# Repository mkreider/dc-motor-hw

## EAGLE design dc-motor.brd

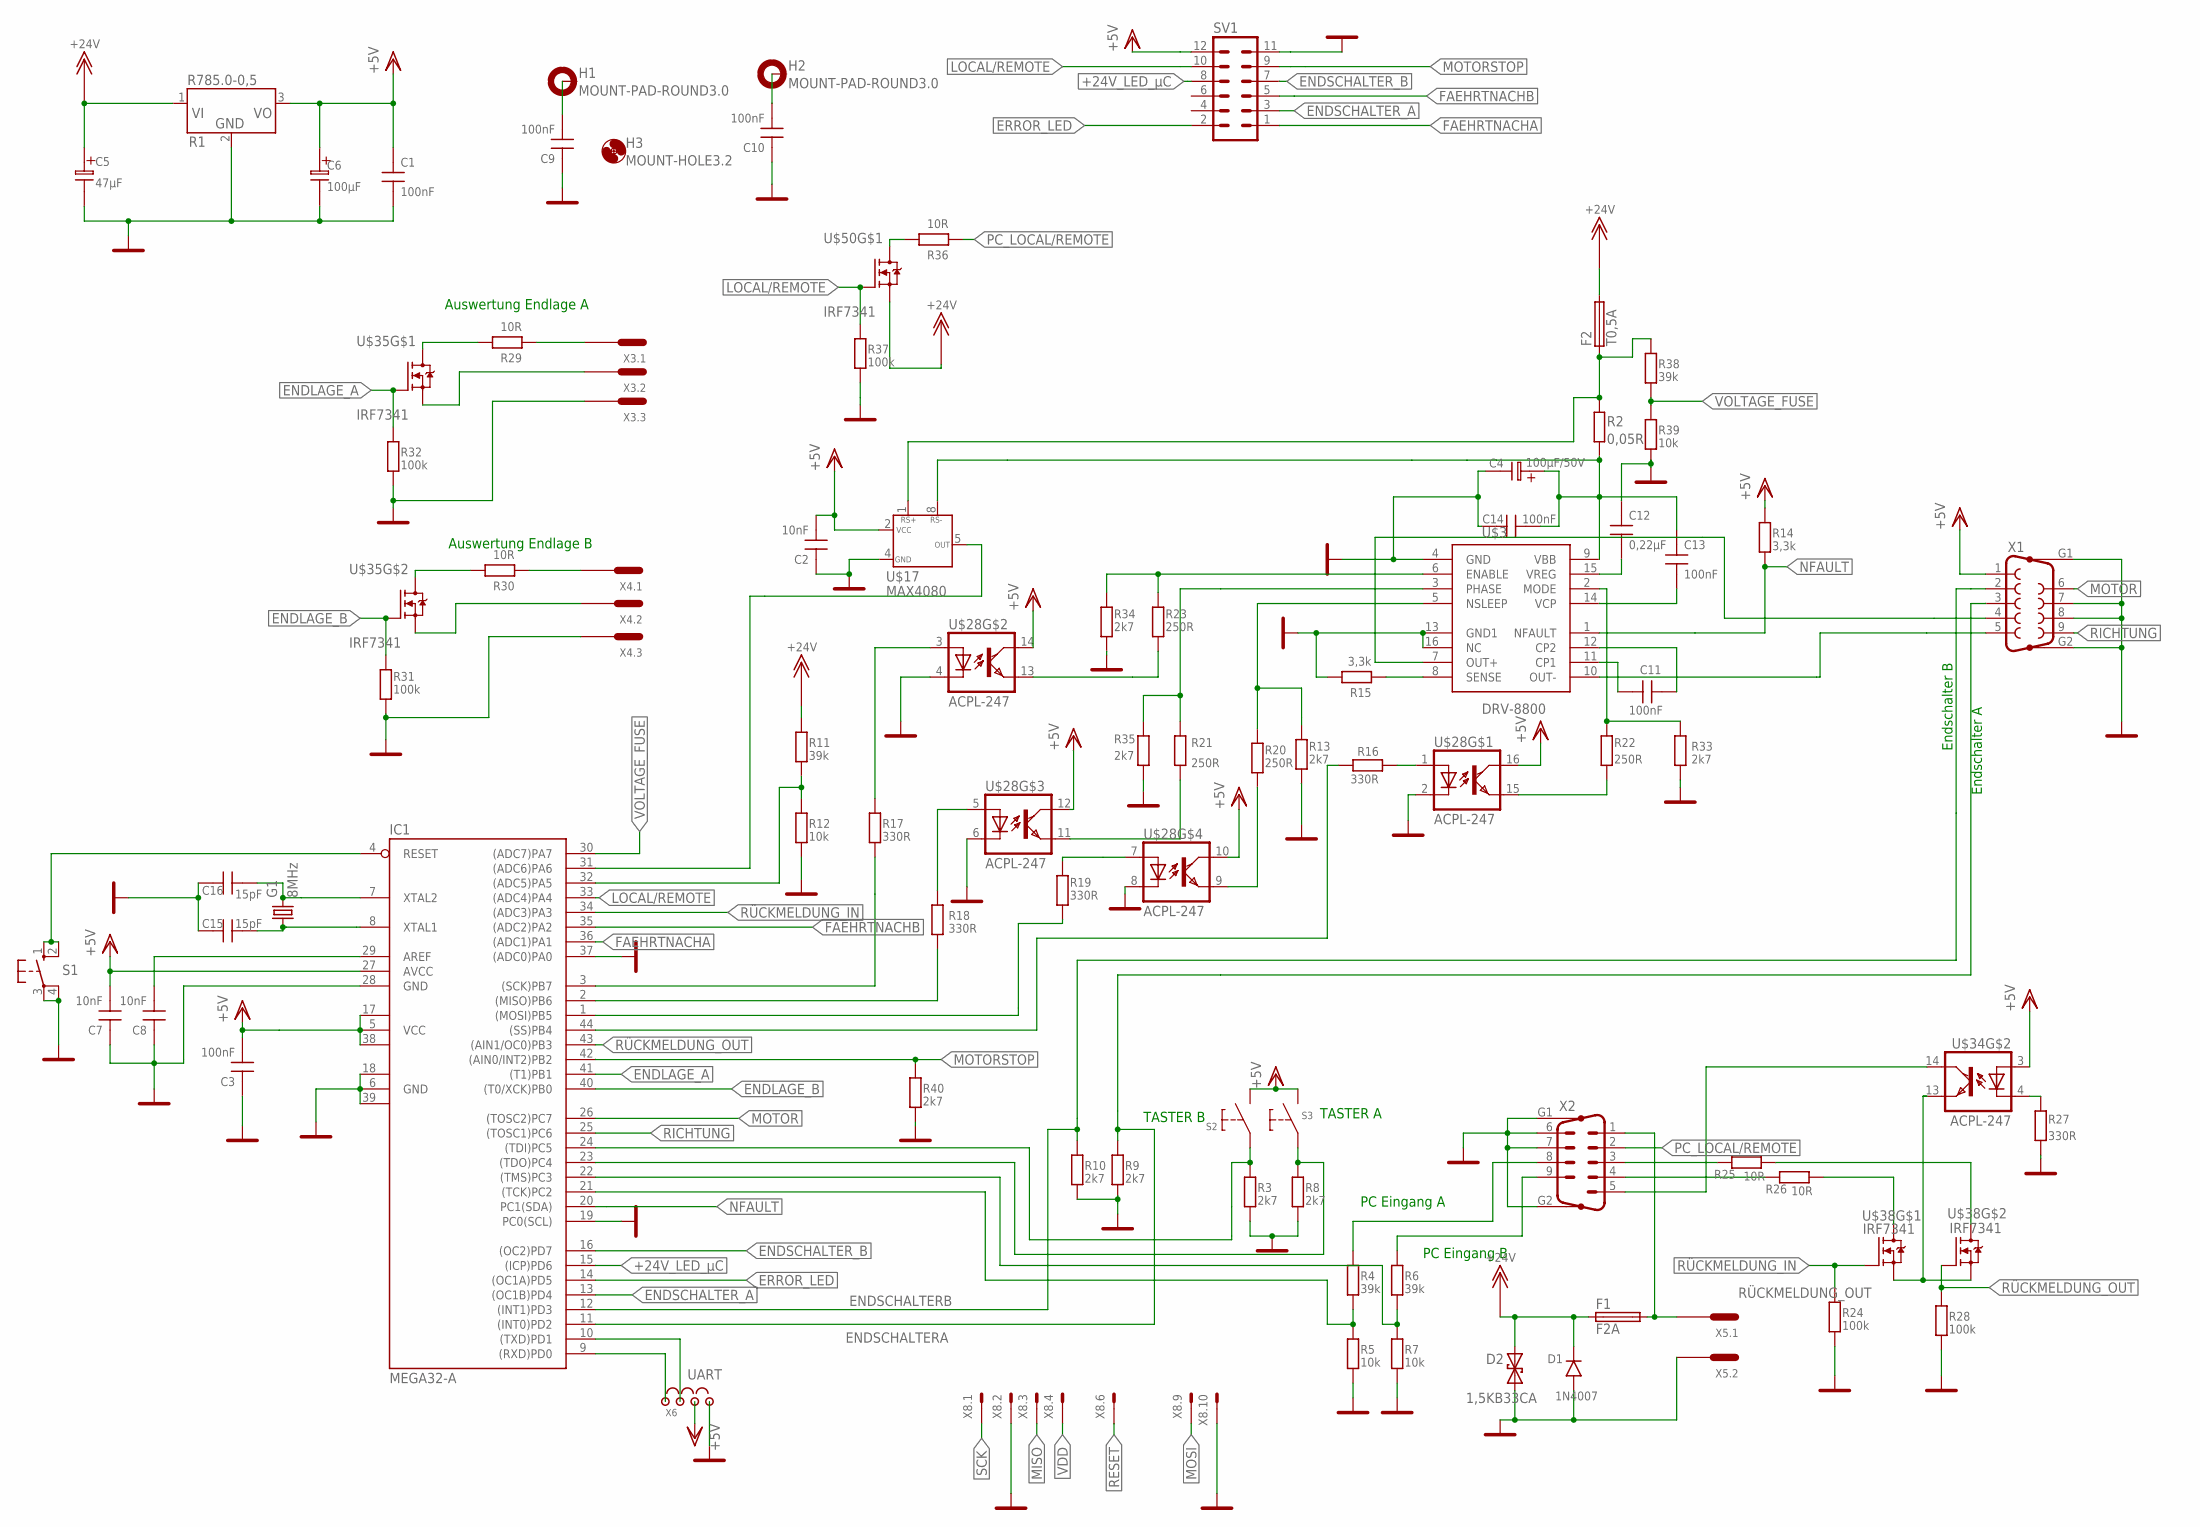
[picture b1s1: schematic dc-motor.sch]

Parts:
C1, C3, C9, C10, C11, C13, C14: 100nF; 0805
C2, C7, C8: 10nF; 0805
C4: 100µF/50V; E5-13
C5: 47µF; E5-13
C6: 100µF; E5-13
C12: 0,22µF; 0805
C15, C16: 15pF; 0805
D1: 1N4007; RM10DR1
D2: 1,5KB33CA; CB417-15
F1: F2A; F457
F2: T0,5A; F457
G1: 8MHz; HC18U-V
H1, H2: MOUNT-PAD-ROUND3.0; 3,0-PAD
H3: MOUNT-HOLE3.2; 3,2
IC1: MEGA32-A; TQFP44; MPN ATMEGA32-16AU
R1: R785.0-0,5; SIP3
R2: 0,05R; SMS-0
R3, R8, R9, R10, R13, R33, R34, R35, R40: 2k7; 0805
R4, R6, R11, R38: 39k; 0805
R5, R7, R12, R39: 10k; 0805
R14, R15: 3,3k; 0805
R16, R17, R18, R19, R27: 330R; 0805
R20, R21, R22, R23: 250R; 0805
R24, R28, R31, R32, R37: 100k; 0805
R25, R26, R29, R30, R36: 10R; 0805
S1: 10-XX; B3F-10XX
S2, S3: DRUCKTASTER_ABGW; 1_POL_ABGW
SV1: MA06-2
U$3: DRV-8800; TSSOP16
U$17: MAX4080
U$28, U$34: ACPL-247; SOIC16
U$35, U$38, U$50: IRF7341; SO08-IRF
X1: F09HP
X2: M09HP
X3, X4: RIA_3POL
X5: RIA_2POL
X6: JUMP1-4
X8: PFVERB10

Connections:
+24V: C5.+, D1.K, D2.C (2), F1.1, F2.2, R1.1, R11.2, U$50.1 (N-S1)
+24V_LED_µC: IC1.15 ((ICP)PD6), SV1.8
ENDLAGE_A: IC1.41 ((T1)PB1), R32.1, U$35.2 (N-G1)
ENDLAGE_B: IC1.40 ((T0/XCK)PB0), R31.1, U$35.4 (N-G1)
ENDSCHALTERA: IC1.11 ((INT0)PD2), R9.2, X1.3
ENDSCHALTERB: IC1.12 ((INT1)PD3), R10.2, X1.2
ENDSCHALTER_A: IC1.13 ((OC1B)PD4), SV1.3
ENDSCHALTER_B: IC1.16 ((OC2)PD7), SV1.7
ERROR_LED: IC1.14 ((OC1A)PD5), SV1.2
FAEHRTNACHA: IC1.36 ((ADC1)PA1), SV1.1
FAEHRTNACHB: IC1.35 ((ADC2)PA2), SV1.5
GND: C1.1, C2.1, C3.1, C4.-, C5.-, C6.-, C7.1, C8.1, C9.1, C10.1, C12.1, C14.1, C15.2, C16.2, D1.A, D2.A (1), IC1.6 (GND), IC1.18 (GND1), IC1.19 (PC0(SCL)), IC1.28 (GND), IC1.37 ((ADC0)PA0), IC1.39 (GND2), R1.2, R3.1, R5.1, R7.1, R8.1, R9.1, R10.1, R12.1, R13.1, R15.2, R24.2, R27.1, R28.2, R31.2, R32.2, R33.1, R34.1, R35.1, R37.2, R39.1, R40.1, S1.3, S1.4 (P1), SV1.11, U$3.4 (GND), U$3.13 (GND1), U$3.16 (NC), U$17.4 (GND), U$28.2 (C), U$28.4 (C), U$28.6 (C), U$28.8 (C), X1.7, X1.8, X1.G1, X1.G2, X2.6, X2.7, X2.G1, X2.G2, X3.P$3, X4.P$3, X5.P$2, X6.4, X8.2, X8.10
LOCAL/REMOTE: IC1.33 ((ADC4)PA4), R37.1, SV1.10, U$50.2 (N-G1)
MISO: IC1.2 ((MISO)PB6), R18.2, X8.3
MOSI: IC1.1 ((MOSI)PB5), R19.1, X8.9
MOTOR: IC1.26 ((TOSC2)PC7), X1.6
MOTORSTOP: IC1.42 ((AIN0/INT2)PB2), R40.2, SV1.9
unnamed: F1.2, X2.1, X5.P$1
unnamed: C15.1, G1.1, IC1.8 (XTAL1)
unnamed: C16.1, G1.2, IC1.7 (XTAL2)
unnamed: IC1.9 ((RXD)PD0), X6.1
unnamed: F2.1, R2.1, R38.2, U$17.1 (RS+)
unnamed: R18.1, U$28.5 (A)
unnamed: IC1.10 ((TXD)PD1), X6.2
unnamed: IC1.21 ((TCK)PC2), R4.1, R5.2
unnamed: IC1.31 ((ADC6)PA6), U$17.5 (OUT)
unnamed: IC1.22 ((TMS)PC3), R6.1, R7.2
unnamed: R6.2, X2.9
unnamed: R4.2, X2.8
unnamed: R20.2, U$28.9 (EMIT)
unnamed: IC1.23 ((TDO)PC4), R8.2, S3.S1 (C)
unnamed: IC1.24 ((TDI)PC5), R3.2, S2.S1 (C)
unnamed: R19.2, U$28.7 (A)
unnamed: IC1.32 ((ADC5)PA5), R11.1, R12.2
unnamed: C9.2, H1.B3,0
unnamed: C10.2, H2.B3,0
unnamed: C11.2, U$3.11 (CP1)
unnamed: C11.1, U$3.12 (CP2)
unnamed: C12.2, U$3.15 (VREG)
unnamed: C13.2, U$3.14 (VCP)
unnamed: R23.1, R34.2, U$3.6 (ENABLE)
unnamed: C4.+, C13.1, C14.2, R2.2, U$3.9 (VBB), U$17.8 (RS-)
unnamed: R13.2, R20.1, U$3.5 (NSLEEP)
unnamed: R22.2, U$28.15 (EMIT)
unnamed: R15.1, U$3.8 (SENSE)
unnamed: U$34.14 (COL), X2.5
unnamed: IC1.44 ((SS)PB4), R16.1
unnamed: R36.2, U$50.7 (D1), U$50.8 (D1)
unnamed: R21.1, R35.2, U$3.3 (PHASE)
unnamed: U$3.7 (OUT+), X1.4
unnamed: R16.2, U$28.1 (A)
unnamed: R17.1, U$28.3 (A)
unnamed: U$3.10 (OUT-), X1.5
unnamed: R23.2, U$28.13 (EMIT)
unnamed: R21.2, U$28.11 (EMIT)
unnamed: R22.1, R33.2, U$3.2 (MODE)
unnamed: R26.2, X2.4
unnamed: R25.2, X2.3
unnamed: U$34.13 (EMIT), U$38.1 (N-S1), U$38.3 (N-S1)
unnamed: R25.1, U$38.5 (D1), U$38.6 (D1)
unnamed: C8.2, IC1.29 (AREF)
unnamed: R27.2, U$34.4 (C)
unnamed: R26.1, U$38.7 (D1), U$38.8 (D1)
unnamed: R29.1, X3.P$1
unnamed: R30.1, X4.P$1
unnamed: R30.2, U$35.5 (D1), U$35.6 (D1)
unnamed: U$35.3 (N-S1), X4.P$2
unnamed: R29.2, U$35.7 (D1), U$35.8 (D1)
unnamed: U$35.1 (N-S1), X3.P$2
NFAULT: IC1.20 (PC1(SDA)), R14.1, U$3.1 (NFAULT)
PC_LOCAL/REMOTE: R36.1, X2.2
RESET: IC1.4 (RESET), S1.1 (S), S1.2 (S1), X8.6
RICHTUNG: IC1.25 ((TOSC1)PC6), X1.9
RÜCKMELDUNG_IN: IC1.34 ((ADC3)PA3), R24.1, U$38.2 (N-G1)
RÜCKMELDUNG_OUT: IC1.43 ((AIN1/OC0)PB3), R28.1, U$38.4 (N-G1)
SCK: IC1.3 ((SCK)PB7), R17.2, X8.1
VDD: C1.2, C2.2, C3.2, C6.+, C7.2, IC1.5 (VCC), IC1.17 (VCC1), IC1.27 (AVCC), IC1.38 (VCC2), R1.3, R14.2, S2.S2 (N0), S3.S2 (N0), SV1.12, U$17.2 (VCC), U$28.10 (COL), U$28.12 (COL), U$28.14 (COL), U$28.16 (COL), U$34.3 (A), X1.1, X6.3, X8.4
VOLTAGE_FUSE: IC1.30 ((ADC7)PA7), R38.1, R39.2

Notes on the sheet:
UART
PC Eingang A
PC Eingang B
TASTER A
TASTER B
Endschalter B
Endschalter A
Auswertung Endlage A
Auswertung Endlage B

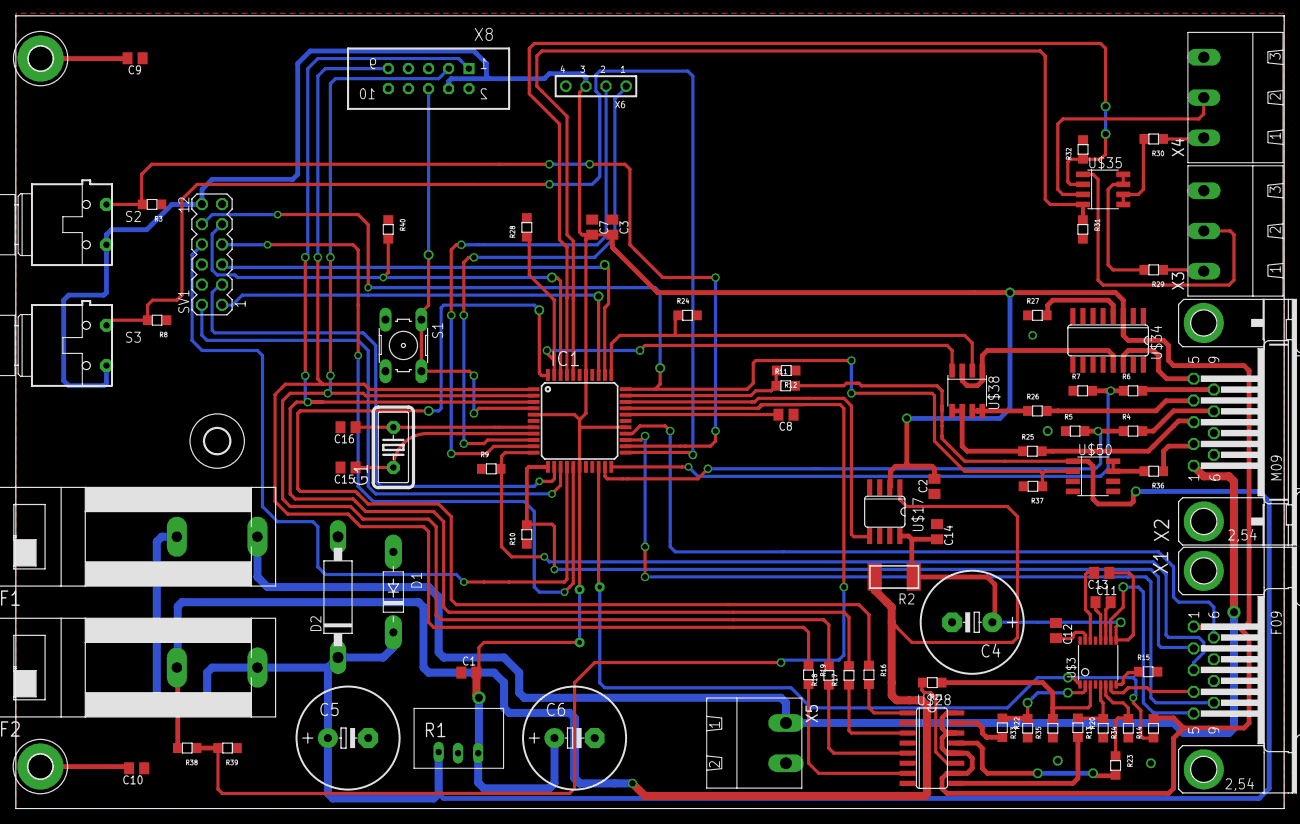
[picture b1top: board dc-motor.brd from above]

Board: 2 copper layers, 160.0 x 100.0 mm, 83 parts (0 on the bottom side), 78 nets.

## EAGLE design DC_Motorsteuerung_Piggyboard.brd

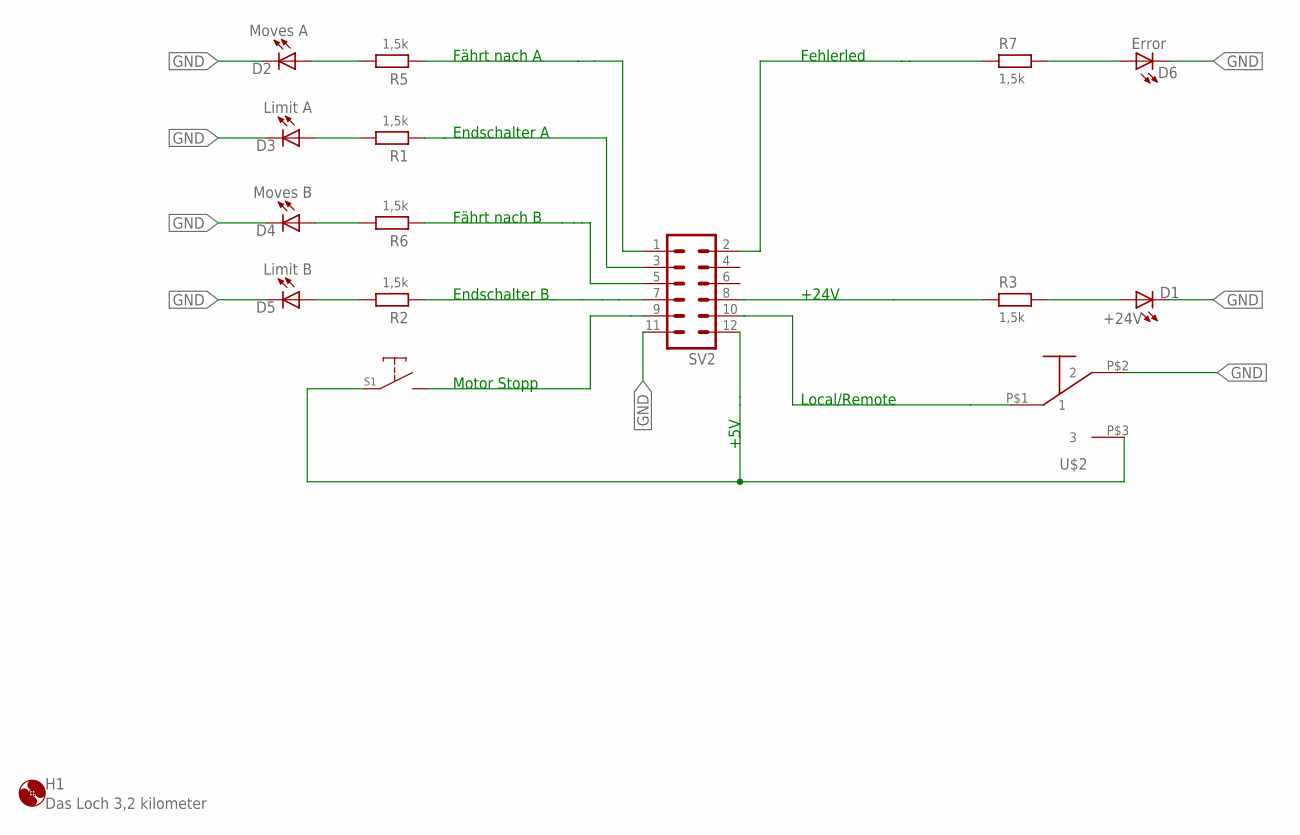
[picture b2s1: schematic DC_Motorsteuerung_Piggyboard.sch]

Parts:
D1: +24V; LED3MMCASE
D2: Moves A; LED3MMCASE
D3: Limit A; LED3MMCASE
D4: Moves B; LED3MMCASE
D5: Limit B; LED3MMCASE
D6: Error; LED3MMCASE
H1: Das Loch 3,2 kilometer; 3,2
R1, R2, R3, R5, R6, R7: 1,5k; R_0,4W
S1: MotorStopp; 1_POL_ABGW
SV2: MA06-2
U$2: UMSCHALTER_SINGLE_POLE

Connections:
GND: D1.P$2 (C), D2.P$2 (C), D3.P$2 (C), D4.P$2 (C), D5.P$2 (C), D6.P$2 (C), SV2.11, U$2.P$2 (2)
unnamed: R2.1, SV2.7
unnamed: D3.P$1 (A), R1.2
unnamed: R1.1, SV2.3
unnamed: D5.P$1 (A), R2.2
unnamed: D6.P$1 (A), R7.2
unnamed: R3.1, SV2.8
unnamed: S1.S2 (N0), SV2.9
unnamed: SV2.10, U$2.P$1 (1)
unnamed: D4.P$1 (A), R6.2
unnamed: S1.S1 (C), SV2.12, U$2.P$3 (3)
unnamed: R5.1, SV2.1
unnamed: D1.P$1 (A), R3.2
unnamed: D2.P$1 (A), R5.2
unnamed: R7.1, SV2.2
unnamed: R6.1, SV2.5

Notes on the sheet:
Motor Stopp
Local/Remote
Fährt nach A
Fährt nach B
+24V
Endschalter A
Endschalter B
+5V
Fehlerled

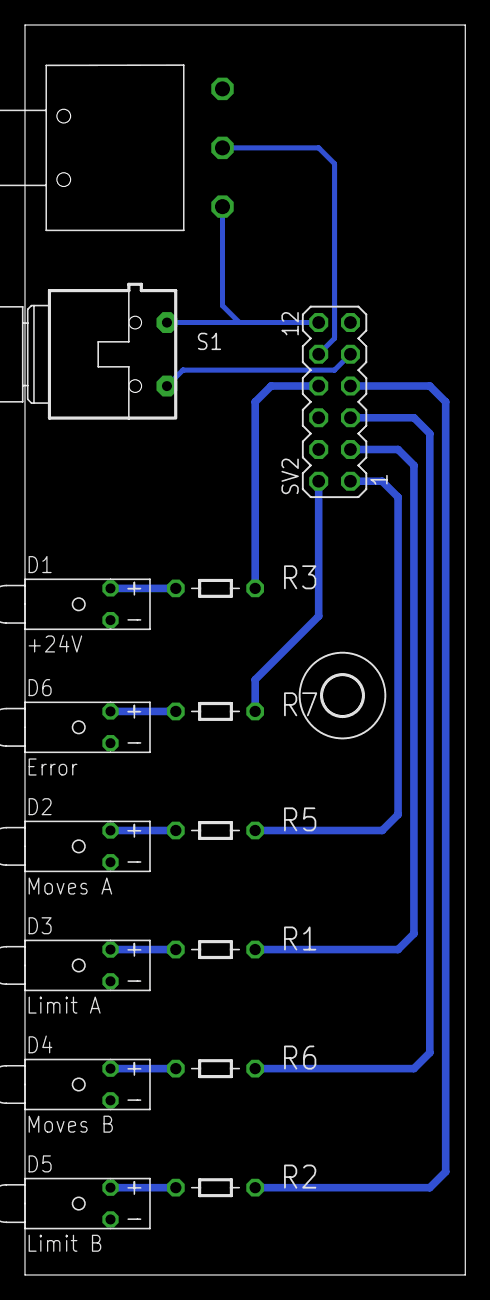
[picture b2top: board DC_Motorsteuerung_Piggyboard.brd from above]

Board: 2 copper layers, 35.2 x 100.0 mm, 16 parts (0 on the bottom side), 16 nets.

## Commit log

2012-11-12 project created
2012-11-12 created eagle project
2012-11-16 Erste Version des Schaltplans (Noch nicht fertig)
2012-11-19 Schaltplan Fertig
2012-11-19 Schaltplan für Piggyboard eingefügt.
2012-11-19 Schaltplan Verbessert und mit dem Layout begonnen
2012-11-19 Schaltplan fast fertiggestellt.
    Umschalter (Taster s2) fehlt
2012-11-19 Schaltplan erweitert
2012-11-21 ADC wiring changed.
2012-11-26 Piggyboard updated
2012-11-27 Layout finished
2012-11-28 layout checked
2012-11-30 Layout fixed
2012-11-30 Piggy board updated (inclusion of Toggle switch )
2012-11-30 Piggyboard incl.
2012-11-30 Piggyboard finished !!
2012-11-30 Piggyboard finished!!
2012-12-05 Piggyboard updated and finished !! (RGB-LED included)
2012-12-05 Layout edited
2012-12-07 test
2012-12-07 edited again
2012-12-07 Motorstop edited
2012-12-10 moved D1 for description on front plate
2012-12-11 Created and added the new front panel.
2012-12-11 Created and added the Specifications, schedule, order list
2012-12-11 Corretur
2012-12-12 Nothing changed
2012-12-12 Switch and RGB-LED
2012-12-12 DC-DC Converter value added
2012-12-14 Created Wide leaves for the documentation
2012-12-14 change and improve the wide leaves
2012-12-14 table of contents added
2012-12-17 RGB_LED killed
2012-12-17 Piggiboard updated (ERROR LED)
2012-12-17 Piggiboard updated
2012-12-17 Piggyboard & Board updated
2012-12-21 Pull Down resistor added
2013-01-16 PWR_LED Connected
2013-01-16 new version
2013-01-16 New version of the documentation
2013-01-16 nothing
2013-01-18 just weired
